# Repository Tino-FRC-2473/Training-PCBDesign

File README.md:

# PCB Design Training

This is a set of lessons introducing basic PCB design using KiCad. We will be making a fun design that blinks LEDs using basic components.

## Setup

KiCad is a free and open source PCB design software. Download and install KiCad from the website: [https://www.kicad.org/download/](https://www.kicad.org/download/).

Next, create a copy of the starter project in this repo.
1. Open KiCad
2. Select File->Clone project from repository
3. Enter Location: `https://github.com/Tino-FRC-2473/Training-PCBDesign.git`
4. Click OK
5. Select a folder to save the project

## Next Steps

Follow these links for the instructions on how to complete your PCB design. Each lesson covers one part of the PCB design process.

1. [Part 1: Schematic](Part1_Schematic.md)
2. [Part 2: PCB Layout](Part2_PCBLayout.md)
3. [Part 3: PCB Routing](Part3_PCBRouting.md)

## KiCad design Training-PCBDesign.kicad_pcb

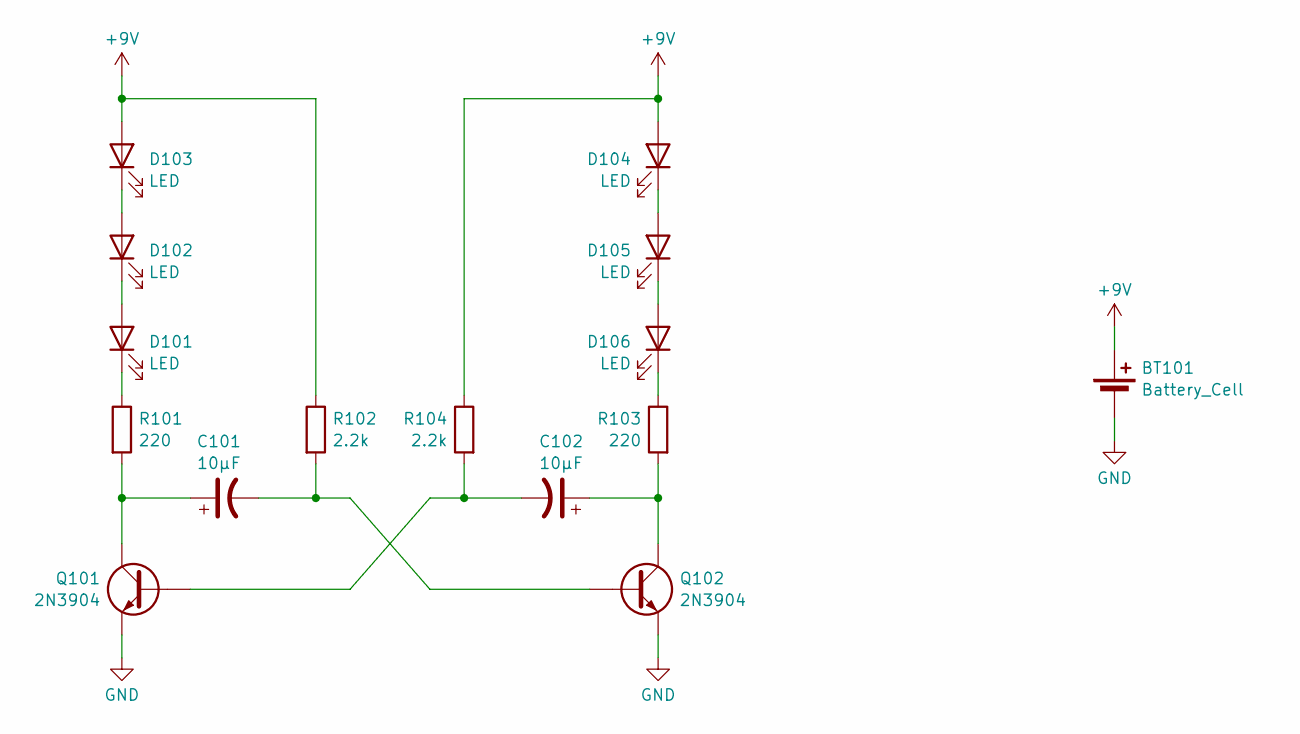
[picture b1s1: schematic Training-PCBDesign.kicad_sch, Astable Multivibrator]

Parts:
BT101: Battery_Cell; PinHeader_1x02_P2.54mm_Vertical
C101, C102: 10µF; CP_Radial_D5.0mm_P2.00mm
D101, D102, D103, D104, D105, D106: LED; LED_D5.0mm
Q101, Q102: 2N3904; TO-92_HandSolder
R101, R103: 220; R_Axial_DIN0207_L6.3mm_D2.5mm_P10.16mm_Horizontal
R102, R104: 2.2k; R_Axial_DIN0207_L6.3mm_D2.5mm_P10.16mm_Horizontal

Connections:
+9V: BT101.1 (+), D103.2 (A), D104.2 (A), R102.1, R104.1
GND: BT101.2 (-), Q101.1 (E), Q102.1 (E)
unnamed: D101.2 (A), D102.1 (K)
unnamed: D101.1 (K), R101.1
unnamed: D102.2 (A), D103.1 (K)
unnamed: D104.1 (K), D105.2 (A)
unnamed: D105.1 (K), D106.2 (A)
unnamed: D106.1 (K), R103.1
unnamed: C102.2, Q101.2 (B), R104.2
unnamed: C101.1, Q101.3 (C), R101.2
unnamed: C101.2, Q102.2 (B), R102.2
unnamed: C102.1, Q102.3 (C), R103.2

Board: 2 copper layers, 15 parts (0 on the bottom side), 12 nets, no tracks yet.

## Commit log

2025-11-09 Assign components
2025-11-11 Add README and lesson files
2025-11-12 Start writing schematic lesson
2025-11-12 Add LED
2025-11-12 Change the LED to 5mm
2025-11-17 Finish schematic instructions
2025-11-17 Start PCB Layout instructions
2025-11-17 Update PCB layout
2025-11-17 Add note about grids
2025-11-17 Add note about bitmap import
